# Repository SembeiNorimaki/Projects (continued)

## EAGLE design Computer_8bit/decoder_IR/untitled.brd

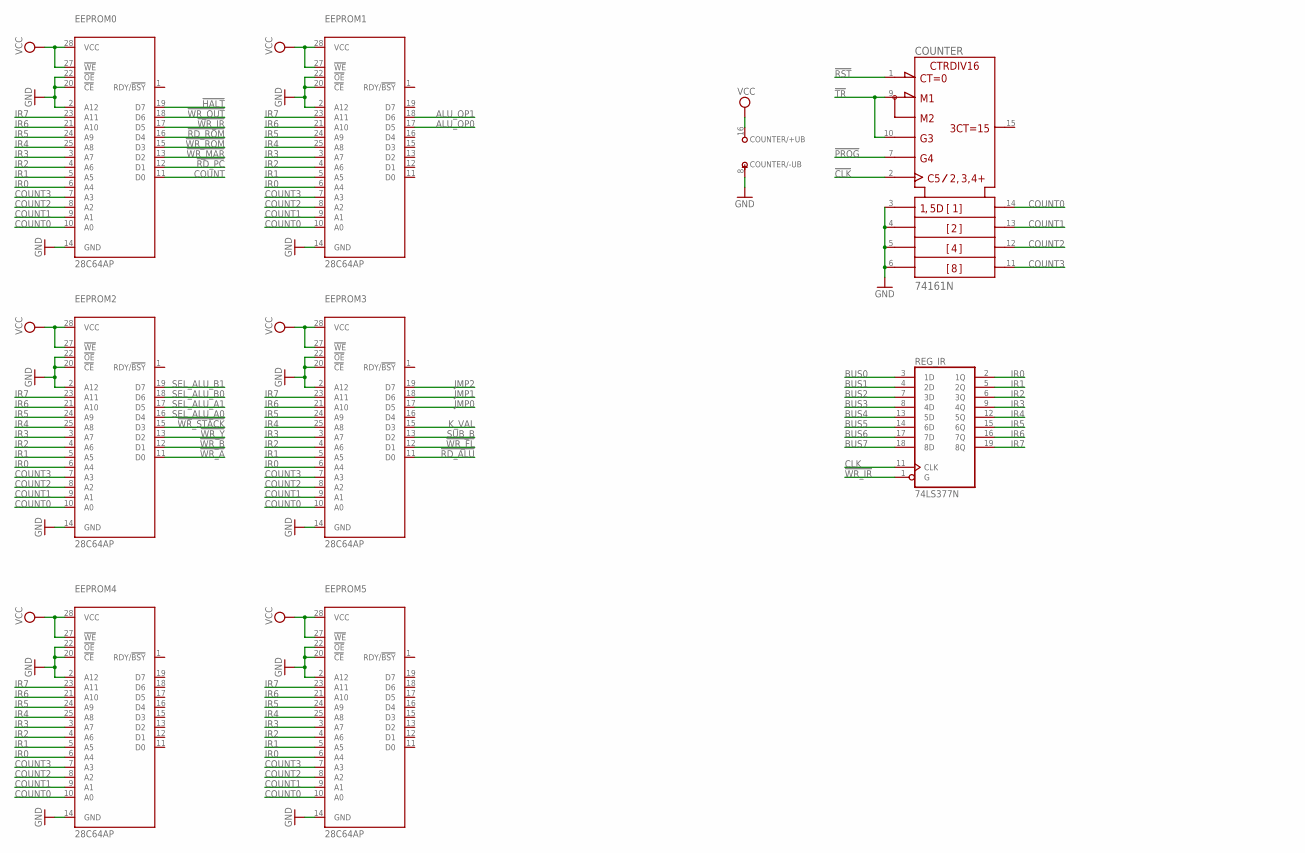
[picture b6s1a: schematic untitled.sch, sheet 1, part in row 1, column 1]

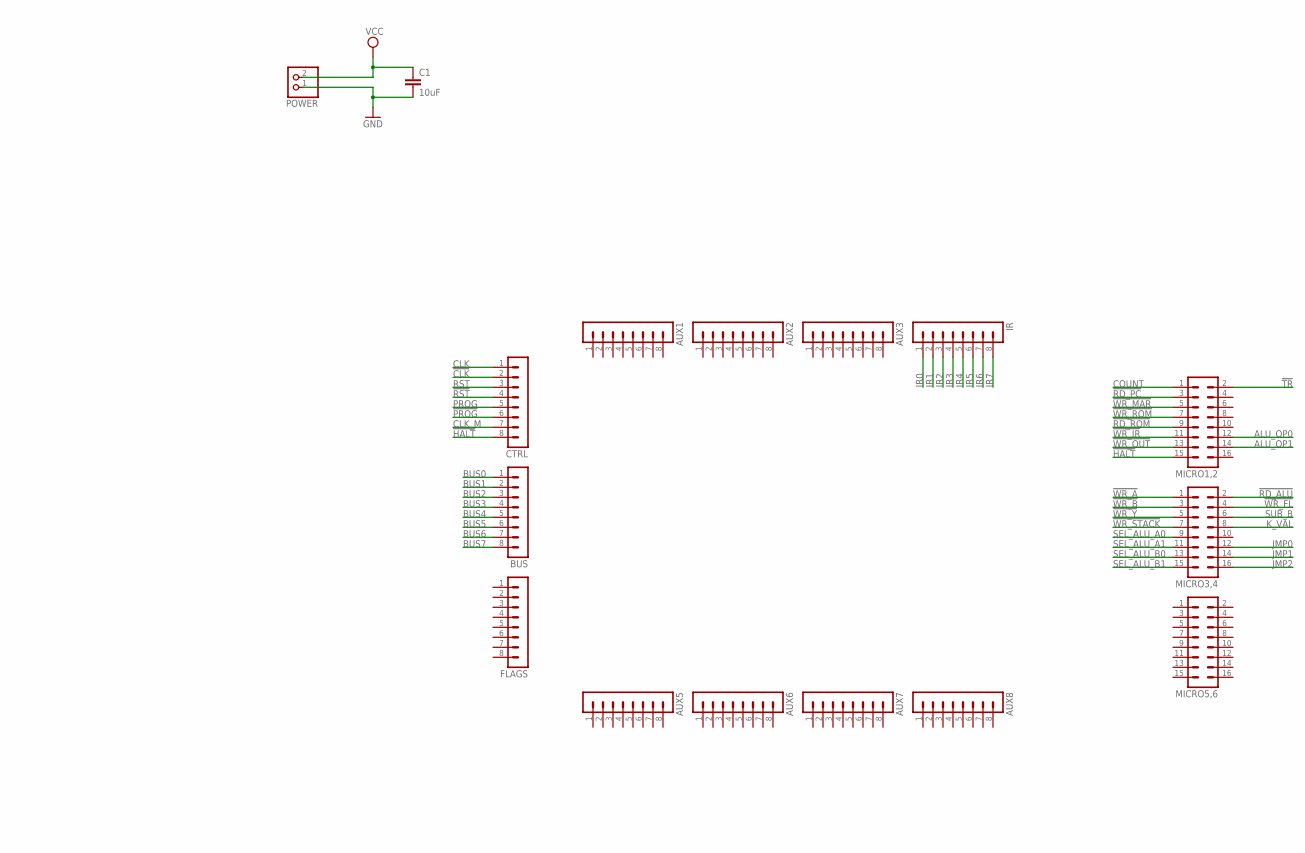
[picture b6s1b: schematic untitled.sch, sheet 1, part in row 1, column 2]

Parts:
AUX1, AUX2, AUX3, AUX5, AUX6, AUX7, AUX8: MA08-1
BUS: MA08-1
C1: 10uF; C025-050X050
COUNTER: 74161N; DIL16
CTRL: MA08-1
EEPROM0, EEPROM1, EEPROM2, EEPROM3, EEPROM4, EEPROM5: 28C64AP; DIL28-6
FLAGS: MA08-1
IR: MA08-1
MICRO1,2, MICRO3,4, MICRO5,6: MA08-2
POWER: PINHD-1X2; 1X02
REG_IR: 74LS377N; DIL20

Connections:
!CLK: COUNTER.2 (CLK), CTRL.2
!HALT: CTRL.8, EEPROM0.19 (D7), MICRO1,2.15
!PROG: COUNTER.7 (ENP), CTRL.6
!RD_ALU: EEPROM3.11 (D0), MICRO3,4.2
!RD_PC: EEPROM0.12 (D1), MICRO1,2.3
!RD_ROM: EEPROM0.16 (D4), MICRO1,2.9
!RST: COUNTER.1 (!CLR), CTRL.4
!TR: COUNTER.9 (!LOAD), COUNTER.10 (ENT), MICRO1,2.2
!WR_A: EEPROM2.11 (D0), MICRO3,4.1
!WR_B: EEPROM2.12 (D1), MICRO3,4.3
!WR_FL: EEPROM3.12 (D1), MICRO3,4.4
!WR_IR: EEPROM0.17 (D5), MICRO1,2.11, REG_IR.1 (G)
!WR_MAR: EEPROM0.13 (D2), MICRO1,2.5
!WR_OUT: EEPROM0.18 (D6), MICRO1,2.13
!WR_ROM: EEPROM0.15 (D3), MICRO1,2.7
!WR_STACK: EEPROM2.15 (D3), MICRO3,4.7
!WR_Y: EEPROM2.13 (D2), MICRO3,4.5
ALU_OP0: EEPROM1.17 (D5), MICRO1,2.12
ALU_OP1: EEPROM1.18 (D6), MICRO1,2.14
BUS0: BUS.1, REG_IR.3 (1D)
BUS1: BUS.2, REG_IR.4 (2D)
BUS2: BUS.3, REG_IR.7 (3D)
BUS3: BUS.4, REG_IR.8 (4D)
BUS4: BUS.5, REG_IR.13 (5D)
BUS5: BUS.6, REG_IR.14 (6D)
BUS6: BUS.7, REG_IR.17 (7D)
BUS7: BUS.8, REG_IR.18 (8D)
CLK: CTRL.1, REG_IR.11 (CLK)
CLK_M: CTRL.7
COUNT: EEPROM0.11 (D0), MICRO1,2.1
COUNT0: COUNTER.14 (QA), EEPROM0.10 (A0), EEPROM1.10 (A0), EEPROM2.10 (A0), EEPROM3.10 (A0), EEPROM4.10 (A0), EEPROM5.10 (A0)
COUNT1: COUNTER.13 (QB), EEPROM0.9 (A1), EEPROM1.9 (A1), EEPROM2.9 (A1), EEPROM3.9 (A1), EEPROM4.9 (A1), EEPROM5.9 (A1)
COUNT2: COUNTER.12 (QC), EEPROM0.8 (A2), EEPROM1.8 (A2), EEPROM2.8 (A2), EEPROM3.8 (A2), EEPROM4.8 (A2), EEPROM5.8 (A2)
COUNT3: COUNTER.11 (QD), EEPROM0.7 (A3), EEPROM1.7 (A3), EEPROM2.7 (A3), EEPROM3.7 (A3), EEPROM4.7 (A3), EEPROM5.7 (A3)
GND: C1.2, COUNTER.3 (A), COUNTER.4 (B), COUNTER.5 (C), COUNTER.6 (D), COUNTER.8 (-UB), EEPROM0.2 (A12), EEPROM0.14 (GND), EEPROM0.20 (!CE), EEPROM0.22 (!OE), EEPROM1.2 (A12), EEPROM1.14 (GND), EEPROM1.20 (!CE), EEPROM1.22 (!OE), EEPROM2.2 (A12), EEPROM2.14 (GND), EEPROM2.20 (!CE), EEPROM2.22 (!OE), EEPROM3.2 (A12), EEPROM3.14 (GND), EEPROM3.20 (!CE), EEPROM3.22 (!OE), EEPROM4.2 (A12), EEPROM4.14 (GND), EEPROM4.20 (!CE), EEPROM4.22 (!OE), EEPROM5.2 (A12), EEPROM5.14 (GND), EEPROM5.20 (!CE), EEPROM5.22 (!OE), POWER.1, REG_IR.10 (GND)
IR0: EEPROM0.6 (A4), EEPROM1.6 (A4), EEPROM2.6 (A4), EEPROM3.6 (A4), EEPROM4.6 (A4), EEPROM5.6 (A4), IR.1, REG_IR.2 (1Q)
IR1: EEPROM0.5 (A5), EEPROM1.5 (A5), EEPROM2.5 (A5), EEPROM3.5 (A5), EEPROM4.5 (A5), EEPROM5.5 (A5), IR.2, REG_IR.5 (2Q)
IR2: EEPROM0.4 (A6), EEPROM1.4 (A6), EEPROM2.4 (A6), EEPROM3.4 (A6), EEPROM4.4 (A6), EEPROM5.4 (A6), IR.3, REG_IR.6 (3Q)
IR3: EEPROM0.3 (A7), EEPROM1.3 (A7), EEPROM2.3 (A7), EEPROM3.3 (A7), EEPROM4.3 (A7), EEPROM5.3 (A7), IR.4, REG_IR.9 (4Q)
IR4: EEPROM0.25 (A8), EEPROM1.25 (A8), EEPROM2.25 (A8), EEPROM3.25 (A8), EEPROM4.25 (A8), EEPROM5.25 (A8), IR.5, REG_IR.12 (5Q)
IR5: EEPROM0.24 (A9), EEPROM1.24 (A9), EEPROM2.24 (A9), EEPROM3.24 (A9), EEPROM4.24 (A9), EEPROM5.24 (A9), IR.6, REG_IR.15 (6Q)
IR6: EEPROM0.21 (A10), EEPROM1.21 (A10), EEPROM2.21 (A10), EEPROM3.21 (A10), EEPROM4.21 (A10), EEPROM5.21 (A10), IR.7, REG_IR.16 (7Q)
IR7: EEPROM0.23 (A11), EEPROM1.23 (A11), EEPROM2.23 (A11), EEPROM3.23 (A11), EEPROM4.23 (A11), EEPROM5.23 (A11), IR.8, REG_IR.19 (8Q)
JMP0: EEPROM3.17 (D5), MICRO3,4.12
JMP1: EEPROM3.18 (D6), MICRO3,4.14
JMP2: EEPROM3.19 (D7), MICRO3,4.16
K_VAL: EEPROM3.15 (D3), MICRO3,4.8
PROG: CTRL.5
RST: CTRL.3
SEL_ALU_A0: EEPROM2.16 (D4), MICRO3,4.9
SEL_ALU_A1: EEPROM2.17 (D5), MICRO3,4.11
SEL_ALU_B0: EEPROM2.18 (D6), MICRO3,4.13
SEL_ALU_B1: EEPROM2.19 (D7), MICRO3,4.15
SUB_B: EEPROM3.13 (D2), MICRO3,4.6
VCC: C1.1, COUNTER.16 (+UB), EEPROM0.27 (!WE), EEPROM0.28 (VCC), EEPROM1.27 (!WE), EEPROM1.28 (VCC), EEPROM2.27 (!WE), EEPROM2.28 (VCC), EEPROM3.27 (!WE), EEPROM3.28 (VCC), EEPROM4.27 (!WE), EEPROM4.28 (VCC), EEPROM5.27 (!WE), EEPROM5.28 (VCC), POWER.2, REG_IR.20 (VCC)

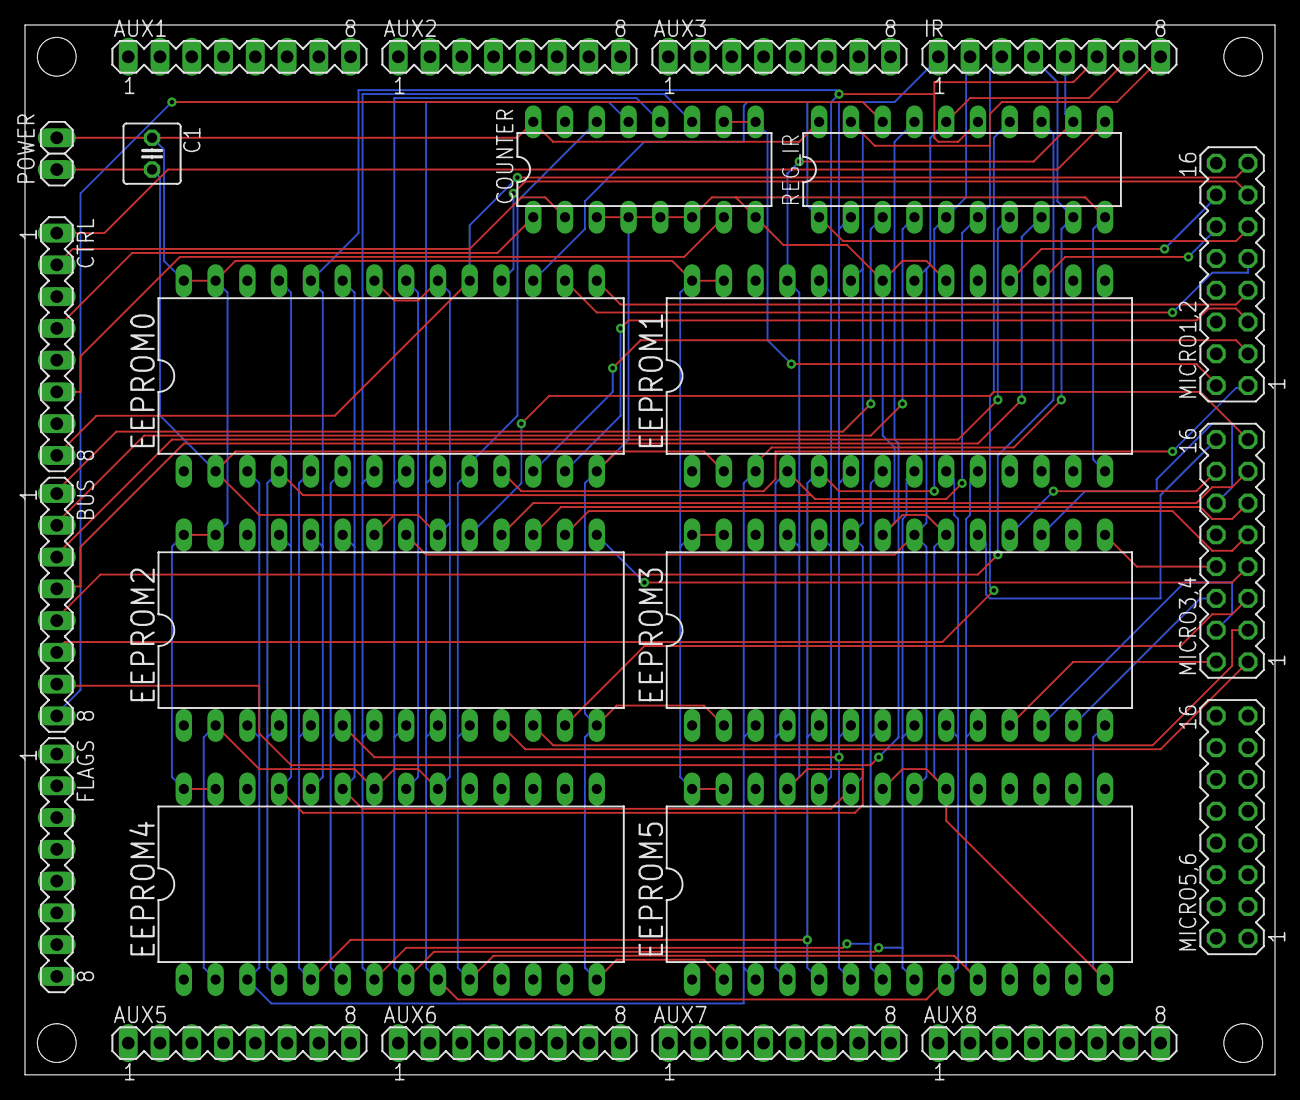
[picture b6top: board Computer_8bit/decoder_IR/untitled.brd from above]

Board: 2 copper layers, 99.9 x 83.9 mm, 24 parts (0 on the bottom side), 52 nets.

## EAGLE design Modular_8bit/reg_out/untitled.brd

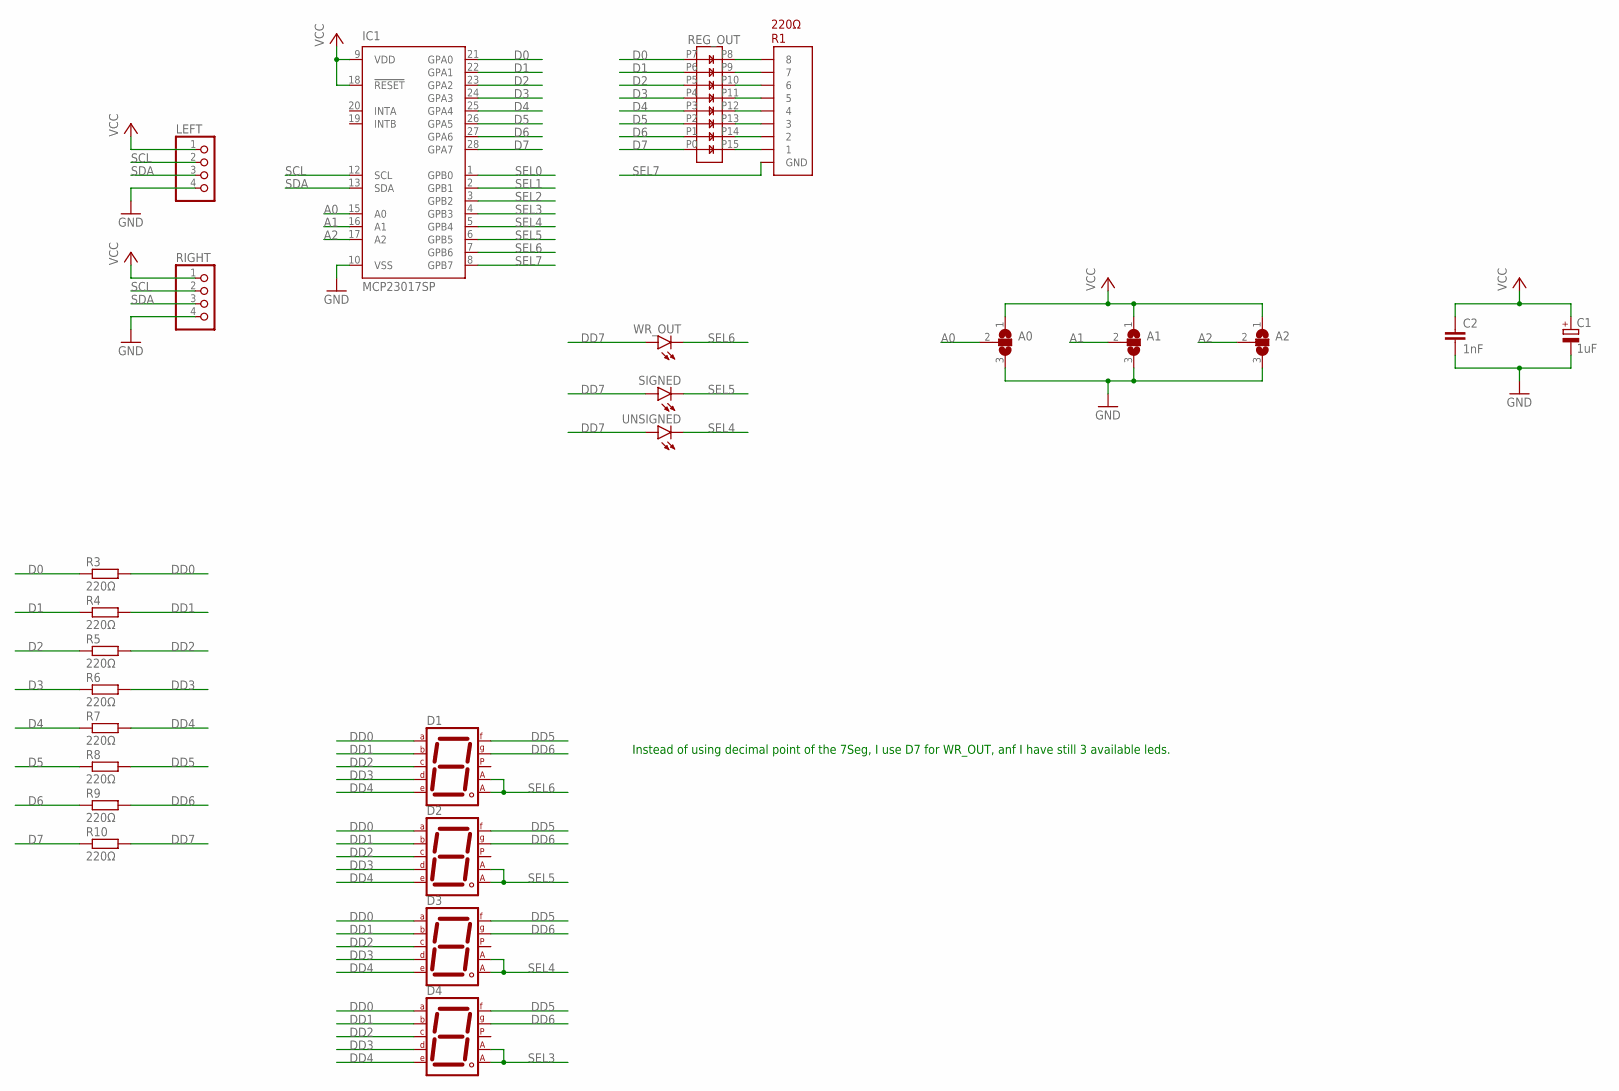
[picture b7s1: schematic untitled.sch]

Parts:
A0, A1, A2: SJ2W; SJ_2
C1: 1uF; E2,5-6
C2: 1nF; C2.5-2
D1, D2, D3, D4: 7SEG-CA; 7SEG-13
IC1: MCP23017SP; DIL28-3
LEFT: PINHD-1X4; 1X04
R1: 220Ω; R_ARRAY_8PIN
R3, R4, R5, R6, R7, R8, R9, R10: 220Ω; 0207/10
REG_OUT: LB8
RIGHT: PINHD-1X4; 1X04
SIGNED: LED3MM
UNSIGNED: LED3MM
WR_OUT: LED3MM

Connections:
A0: A0.2, IC1.15 (A0)
A1: A1.2, IC1.16 (A1)
A2: A2.2, IC1.17 (A2)
D0: IC1.21 (GPA0), R3.1, REG_OUT.P7
D1: IC1.22 (GPA1), R4.1, REG_OUT.P6
D2: IC1.23 (GPA2), R5.1, REG_OUT.P5
D3: IC1.24 (GPA3), R6.1, REG_OUT.P4
D4: IC1.25 (GPA4), R7.1, REG_OUT.P3
D5: IC1.26 (GPA5), R8.1, REG_OUT.P2
D6: IC1.27 (GPA6), R9.1, REG_OUT.P1
D7: IC1.28 (GPA7), R10.1, REG_OUT.P0
DD0: D1.7 (A), D2.7 (A), D3.7 (A), D4.7 (A), R3.2
DD1: D1.6 (B), D2.6 (B), D3.6 (B), D4.6 (B), R4.2
DD2: D1.4 (C), D2.4 (C), D3.4 (C), D4.4 (C), R5.2
DD3: D1.2 (D), D2.2 (D), D3.2 (D), D4.2 (D), R6.2
DD4: D1.1 (E), D2.1 (E), D3.1 (E), D4.1 (E), R7.2
DD5: D1.9 (F), D2.9 (F), D3.9 (F), D4.9 (F), R8.2
DD6: D1.10 (G), D2.10 (G), D3.10 (G), D4.10 (G), R9.2
DD7: R10.2, SIGNED.A, UNSIGNED.A, WR_OUT.A
GND: A0.3, A1.3, A2.3, C1.-, C2.2, IC1.10 (VSS), LEFT.4, RIGHT.4
unnamed: R1.8, REG_OUT.P8
unnamed: R1.7, REG_OUT.P9
unnamed: R1.6, REG_OUT.P10
unnamed: R1.5, REG_OUT.P11
unnamed: R1.4, REG_OUT.P12
unnamed: R1.3, REG_OUT.P13
unnamed: R1.2, REG_OUT.P14
unnamed: R1.1, REG_OUT.P15
SCL: IC1.12 (SCL), LEFT.2, RIGHT.2
SDA: IC1.13 (SDA), LEFT.3, RIGHT.3
SEL0: IC1.1 (GPB0)
SEL1: IC1.2 (GPB1)
SEL2: IC1.3 (GPB2)
SEL3: D4.3 (CA1), D4.8 (CA2), IC1.4 (GPB3)
SEL4: D3.3 (CA1), D3.8 (CA2), IC1.5 (GPB4), UNSIGNED.K (C)
SEL5: D2.3 (CA1), D2.8 (CA2), IC1.6 (GPB5), SIGNED.K (C)
SEL6: D1.3 (CA1), D1.8 (CA2), IC1.7 (GPB6), WR_OUT.K (C)
SEL7: IC1.8 (GPB7), R1.GND
VCC: A0.1, A1.1, A2.1, C1.+, C2.1, IC1.9 (VDD), IC1.18 (!RESET), LEFT.1, RIGHT.1

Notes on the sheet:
Instead of using decimal point of the 7Seg, I use D7 for WR_OUT, anf I have still 3 available leds.

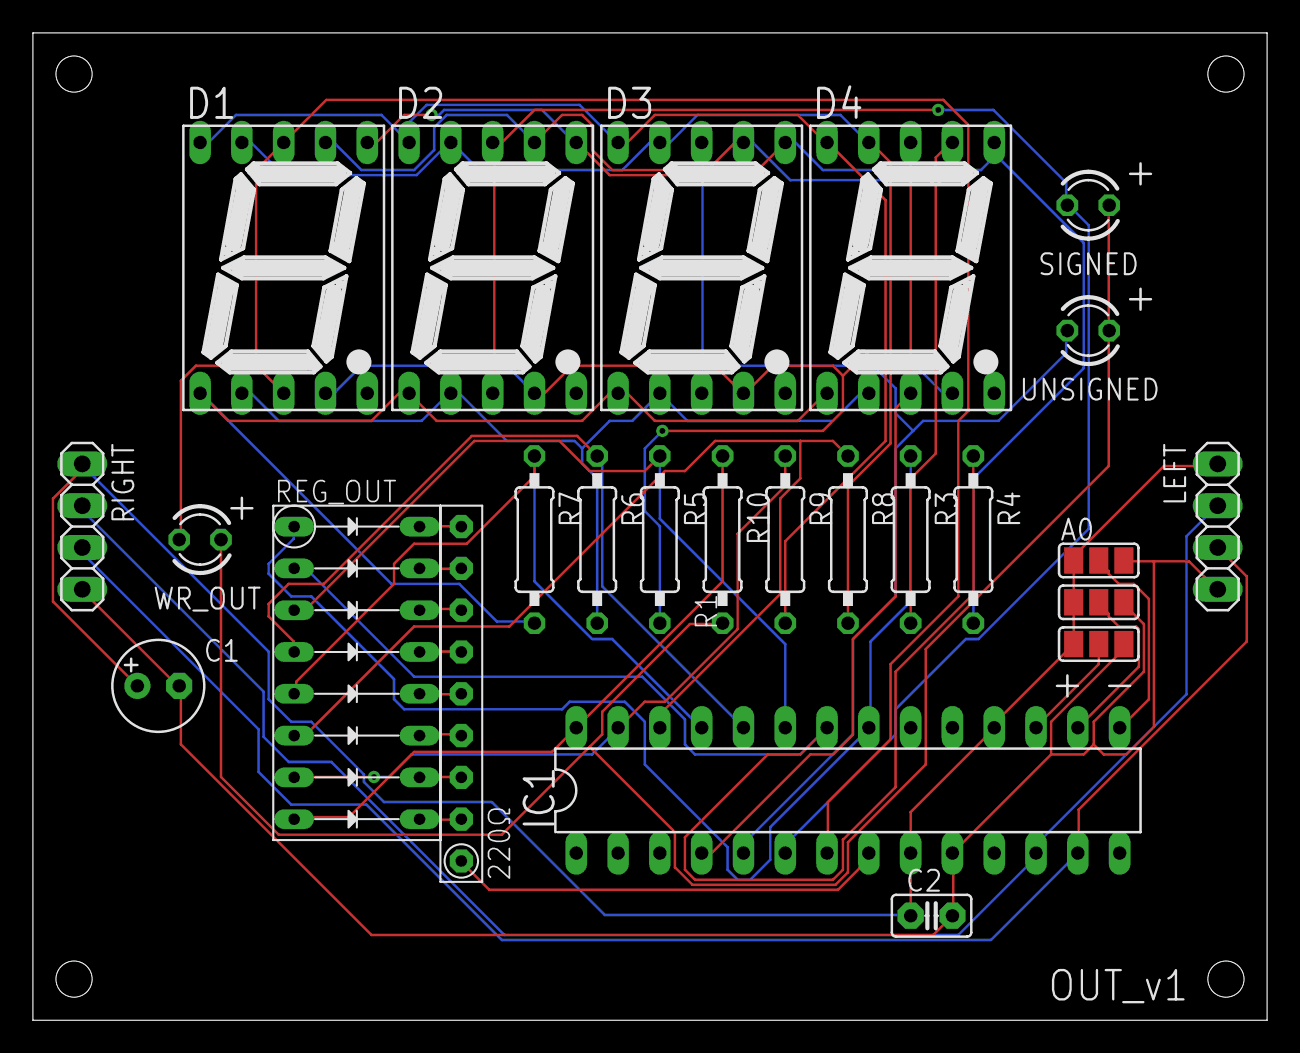
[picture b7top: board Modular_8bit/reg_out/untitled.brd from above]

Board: 2 copper layers, 75.0 x 60.0 mm, 25 parts (0 on the bottom side), 36 nets.

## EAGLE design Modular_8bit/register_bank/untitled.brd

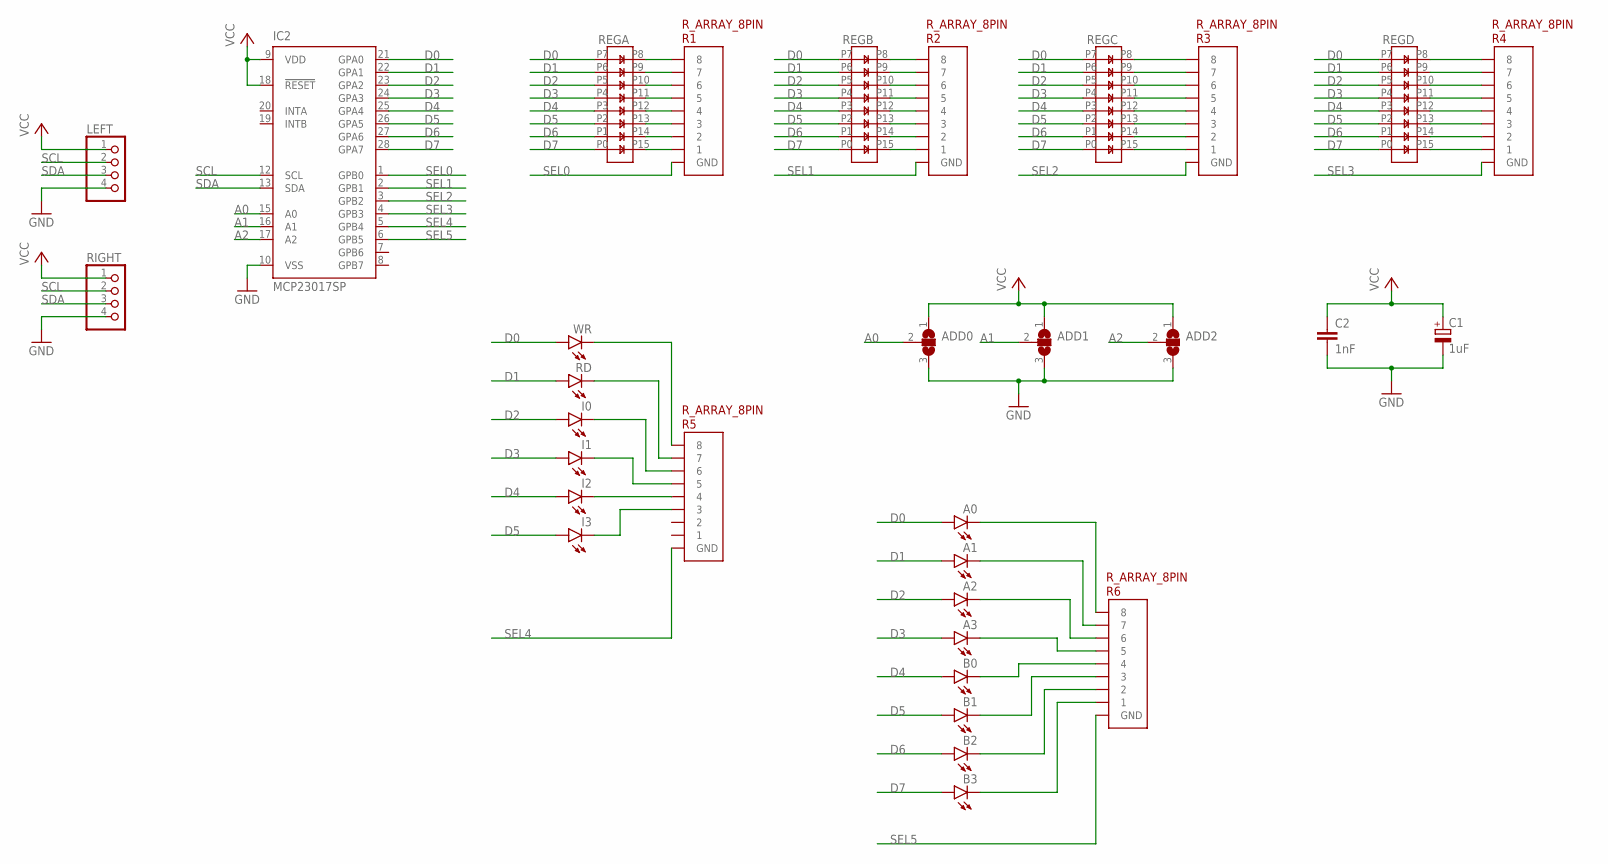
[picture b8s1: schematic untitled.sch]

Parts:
A0, A1, A2, A3: LED3MM
ADD0, ADD1, ADD2: SJ2W; SJ_2
B0, B1, B2, B3: LED3MM
C1: 1uF; E2,5-6
C2: 1nF; C2.5-2
I0, I1, I2, I3: LED3MM
IC2: MCP23017SP; DIL28-3
LEFT: PINHD-1X4; 1X04
R1, R2, R3, R4, R5, R6: R_ARRAY_8PIN
RD: LED3MM
REGA: LB8
REGB: LB8
REGC: LB8
REGD: LB8
RIGHT: PINHD-1X4; 1X04
WR: LED3MM

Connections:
A0: ADD0.2, IC2.15 (A0)
A1: ADD1.2, IC2.16 (A1)
A2: ADD2.2, IC2.17 (A2)
D0: A0.A, IC2.21 (GPA0), REGA.P7, REGB.P7, REGC.P7, REGD.P7, WR.A
D1: A1.A, IC2.22 (GPA1), RD.A, REGA.P6, REGB.P6, REGC.P6, REGD.P6
D2: A2.A, I0.A, IC2.23 (GPA2), REGA.P5, REGB.P5, REGC.P5, REGD.P5
D3: A3.A, I1.A, IC2.24 (GPA3), REGA.P4, REGB.P4, REGC.P4, REGD.P4
D4: B0.A, I2.A, IC2.25 (GPA4), REGA.P3, REGB.P3, REGC.P3, REGD.P3
D5: B1.A, I3.A, IC2.26 (GPA5), REGA.P2, REGB.P2, REGC.P2, REGD.P2
D6: B2.A, IC2.27 (GPA6), REGA.P1, REGB.P1, REGC.P1, REGD.P1
D7: B3.A, IC2.28 (GPA7), REGA.P0, REGB.P0, REGC.P0, REGD.P0
GND: ADD0.3, ADD1.3, ADD2.3, C1.-, C2.2, IC2.10 (VSS), LEFT.4, RIGHT.4
unnamed: R3.8, REGC.P8
unnamed: R3.7, REGC.P9
unnamed: R3.6, REGC.P10
unnamed: R3.5, REGC.P11
unnamed: R3.4, REGC.P12
unnamed: R3.3, REGC.P13
unnamed: R3.2, REGC.P14
unnamed: R3.1, REGC.P15
unnamed: R5.8, WR.K (C)
unnamed: R5.7, RD.K (C)
unnamed: I0.K (C), R5.6
unnamed: I1.K (C), R5.5
unnamed: I2.K (C), R5.4
unnamed: I3.K (C), R5.3
unnamed: R1.8, REGA.P8
unnamed: R1.7, REGA.P9
unnamed: R1.6, REGA.P10
unnamed: R1.5, REGA.P11
unnamed: R1.4, REGA.P12
unnamed: R1.3, REGA.P13
unnamed: R1.2, REGA.P14
unnamed: R1.1, REGA.P15
unnamed: R2.8, REGB.P8
unnamed: R2.7, REGB.P9
unnamed: R2.6, REGB.P10
unnamed: R2.5, REGB.P11
unnamed: R2.4, REGB.P12
unnamed: R2.3, REGB.P13
unnamed: R2.2, REGB.P14
unnamed: R2.1, REGB.P15
unnamed: A0.K (C), R6.8
unnamed: A1.K (C), R6.7
unnamed: A2.K (C), R6.6
unnamed: A3.K (C), R6.5
unnamed: R4.8, REGD.P8
unnamed: R4.7, REGD.P9
unnamed: R4.6, REGD.P10
unnamed: R4.5, REGD.P11
unnamed: R4.4, REGD.P12
unnamed: R4.3, REGD.P13
unnamed: R4.2, REGD.P14
unnamed: R4.1, REGD.P15
unnamed: B0.K (C), R6.4
unnamed: B1.K (C), R6.3
unnamed: B2.K (C), R6.2
unnamed: B3.K (C), R6.1
SCL: IC2.12 (SCL), LEFT.2, RIGHT.2
SDA: IC2.13 (SDA), LEFT.3, RIGHT.3
SEL0: IC2.1 (GPB0), R1.GND
SEL1: IC2.2 (GPB1), R2.GND
SEL2: IC2.3 (GPB2), R3.GND
SEL3: IC2.4 (GPB3), R4.GND
SEL4: IC2.5 (GPB4), R5.GND
SEL5: IC2.6 (GPB5), R6.GND
VCC: ADD0.1, ADD1.1, ADD2.1, C1.+, C2.1, IC2.9 (VDD), IC2.18 (!RESET), LEFT.1, RIGHT.1

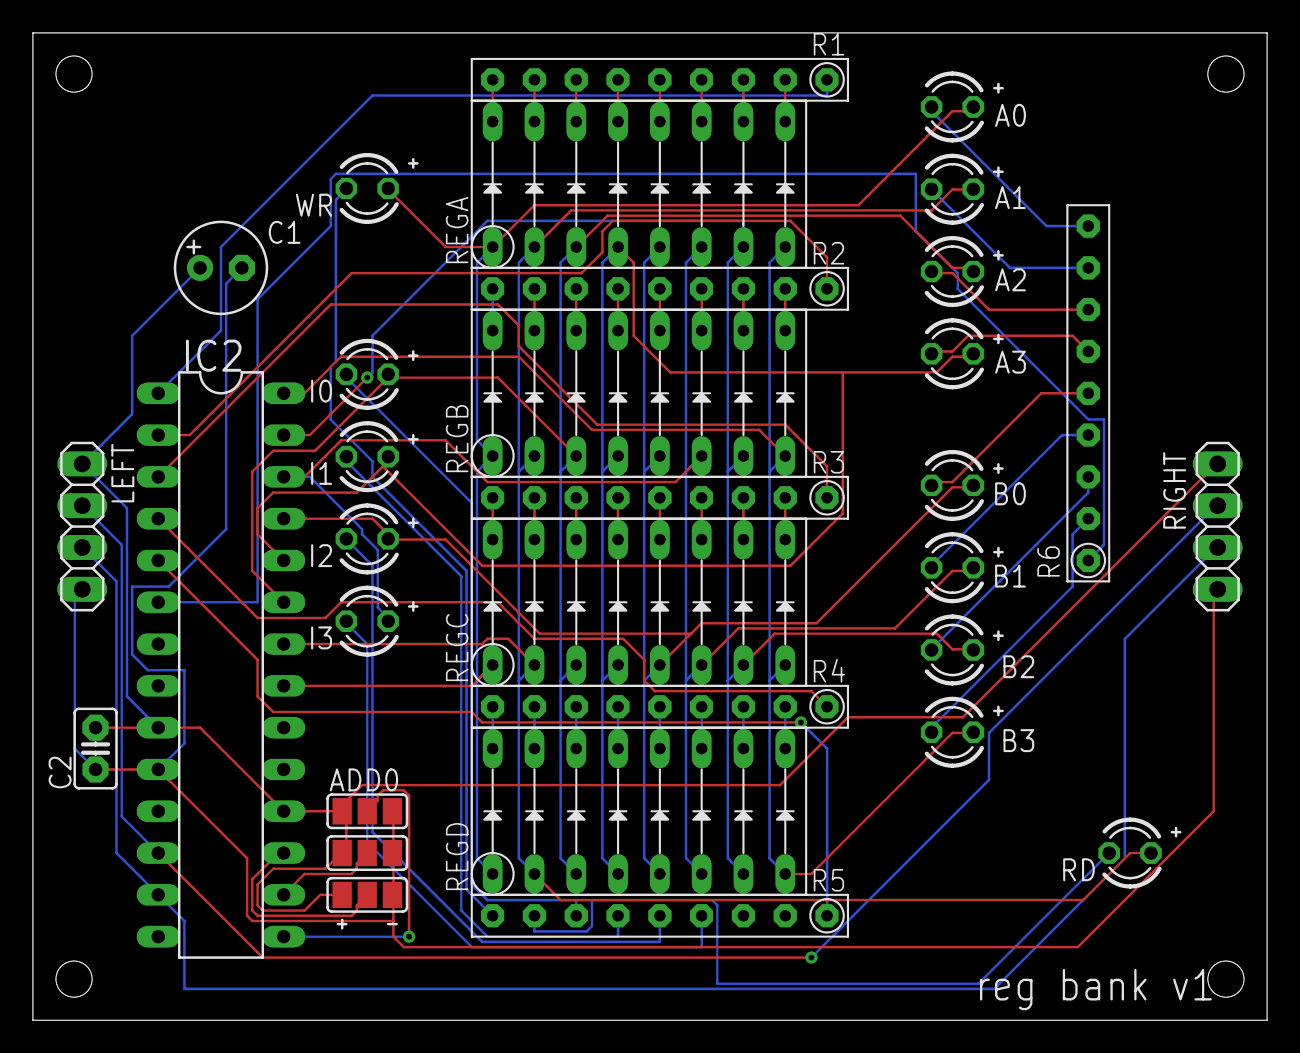
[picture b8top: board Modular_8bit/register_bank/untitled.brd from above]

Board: 2 copper layers, 75.0 x 60.0 mm, 32 parts (0 on the bottom side), 67 nets.

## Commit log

2016-10-26 Github commit test
2016-10-26 test github2
2016-10-26 test github
2017-07-21 Structure
2017-07-26 fritzing
2020-09-16 Cleaned folder
2020-09-16 Dragon Ball
2020-09-16 Hydroponics
2020-09-16 Time glove
2020-09-16 Planetes project
2020-09-16 Modular 8bit
2020-09-16 8bit computer
2020-09-16 MyPrusaBear
2020-09-16 Nile Game
2020-09-16 Robot 4WD
2020-09-16 Prusa
2020-10-05 Added Class Radar
2020-10-08 DragonBall added BT functionalities
2020-10-09 Bluetooth pairing and exchange of data
2020-10-12 Compass methods
2020-11-09 Refactoring, improvements
2020-11-09 Learn German App
2021-01-15 Electronic kit
2021-01-28 Electronic modules implementation
2021-01-29 Modular Kit code
2021-04-01 Bump y18n from 4.0.0 to 4.0.1 in /LearnGerman
    Bumps [y18n](https://github.com/yargs/y18n) from 4.0.0 to 4.0.1.
    - [Release notes](https://github.com/yargs/y18n/releases)
    - [Changelog](https://github.com/yargs/y18n/blob/master/CHANGELOG.md)
    - [Commits](https://github.com/yargs/y18n/commits)
2021-05-08 Bump ua-parser-js from 0.7.22 to 0.7.28 in /LearnGerman
    Bumps [ua-parser-js](https://github.com/faisalman/ua-parser-js) from 0.7.22 to 0.7.28.
    - [Release notes](https://github.com/faisalman/ua-parser-js/releases)
    - [Commits](https://github.com/faisalman/ua-parser-js/compare/0.7.22...0.7.28)
2021-05-11 Bump hosted-git-info from 2.8.8 to 2.8.9 in /LearnGerman
    Bumps [hosted-git-info](https://github.com/npm/hosted-git-info) from 2.8.8 to 2.8.9.
    - [Release notes](https://github.com/npm/hosted-git-info/releases)
    - [Changelog](https://github.com/npm/hosted-git-info/blob/v2.8.9/CHANGELOG.md)
    - [Commits](https://github.com/npm/hosted-git-info/compare/v2.8.8...v2.8.9)
2021-05-11 Bump lodash from 4.17.20 to 4.17.21 in /LearnGerman
    Bumps [lodash](https://github.com/lodash/lodash) from 4.17.20 to 4.17.21.
    - [Release notes](https://github.com/lodash/lodash/releases)
    - [Commits](https://github.com/lodash/lodash/compare/4.17.20...4.17.21)
2021-06-12 Bump glob-parent from 5.1.1 to 5.1.2 in /LearnGerman
    Bumps [glob-parent](https://github.com/gulpjs/glob-parent) from 5.1.1 to 5.1.2.
    - [Release notes](https://github.com/gulpjs/glob-parent/releases)
    - [Changelog](https://github.com/gulpjs/glob-parent/blob/main/CHANGELOG.md)
    - [Commits](https://github.com/gulpjs/glob-parent/compare/v5.1.1...v5.1.2)
    ---
    updated-dependencies:
2021-07-20 Bump react-native from 0.63.2 to 0.64.1 in /LearnGerman
    Bumps [react-native](https://github.com/facebook/react-native) from 0.63.2 to 0.64.1.
    - [Release notes](https://github.com/facebook/react-native/releases)
    - [Changelog](https://github.com/facebook/react-native/blob/main/Releases.md)
    - [Commits](https://github.com/facebook/react-native/compare/v0.63.2...v0.64.1)
    ---
    updated-dependencies:
2021-08-12 Bump path-parse from 1.0.6 to 1.0.7 in /LearnGerman
    Bumps [path-parse](https://github.com/jbgutierrez/path-parse) from 1.0.6 to 1.0.7.
    - [Release notes](https://github.com/jbgutierrez/path-parse/releases)
    - [Commits](https://github.com/jbgutierrez/path-parse/commits/v1.0.7)
    ---
    updated-dependencies:
    - dependency-name: path-parse
2021-09-22 Bump tmpl from 1.0.4 to 1.0.5 in /LearnGerman
    Bumps [tmpl](https://github.com/daaku/nodejs-tmpl) from 1.0.4 to 1.0.5.
    - [Release notes](https://github.com/daaku/nodejs-tmpl/releases)
    - [Commits](https://github.com/daaku/nodejs-tmpl/commits/v1.0.5)
    ---
    updated-dependencies:
    - dependency-name: tmpl
2022-01-22 Bump nanoid from 3.1.12 to 3.2.0 in /LearnGerman
    Bumps [nanoid](https://github.com/ai/nanoid) from 3.1.12 to 3.2.0.
    - [Release notes](https://github.com/ai/nanoid/releases)
    - [Changelog](https://github.com/ai/nanoid/blob/main/CHANGELOG.md)
    - [Commits](https://github.com/ai/nanoid/compare/3.1.12...3.2.0)
    ---
    updated-dependencies:
2022-03-02 Bump plist from 3.0.1 to 3.0.4 in /LearnGerman
    Bumps [plist](https://github.com/TooTallNate/node-plist) from 3.0.1 to 3.0.4.
    - [Release notes](https://github.com/TooTallNate/node-plist/releases)
    - [Changelog](https://github.com/TooTallNate/plist.js/blob/master/History.md)
    - [Commits](https://github.com/TooTallNate/node-plist/commits)
    ---
    updated-dependencies:
2022-03-28 Bump minimist from 1.2.5 to 1.2.6 in /LearnGerman
    Bumps [minimist](https://github.com/substack/minimist) from 1.2.5 to 1.2.6.
    - [Release notes](https://github.com/substack/minimist/releases)
    - [Commits](https://github.com/substack/minimist/compare/1.2.5...1.2.6)
    ---
    updated-dependencies:
    - dependency-name: minimist
2022-04-29 Bump async from 2.6.3 to 2.6.4 in /LearnGerman
    Bumps [async](https://github.com/caolan/async) from 2.6.3 to 2.6.4.
    - [Release notes](https://github.com/caolan/async/releases)
    - [Changelog](https://github.com/caolan/async/blob/v2.6.4/CHANGELOG.md)
    - [Commits](https://github.com/caolan/async/compare/v2.6.3...v2.6.4)
    ---
    updated-dependencies:
2022-06-02 Bump simple-plist from 1.1.0 to 1.3.1 in /LearnGerman
    Bumps [simple-plist](https://github.com/wollardj/simple-plist) from 1.1.0 to 1.3.1.
    - [Release notes](https://github.com/wollardj/simple-plist/releases)
    - [Commits](https://github.com/wollardj/simple-plist/compare/1.1.0...v1.3.1)
    ---
    updated-dependencies:
    - dependency-name: simple-plist
2022-10-12 Bump xmldom and plist in /LearnGerman
    Removes [xmldom](https://github.com/xmldom/xmldom). It's no longer used after updating ancestor dependency [plist](https://github.com/TooTallNate/node-plist). These dependencies need to be updated to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
    Removes `xmldom`
    Updates `plist` from 3.0.1 to 3.0.6
    - [Release notes](https://github.com/TooTallNate/node-plist/releases)
    - [Changelog](https://github.com/TooTallNate/plist.js/blob/master/History.md)
    - [Commits](https://github.com/TooTallNate/node-plist/commits)
2022-10-21 Bump react-native-reanimated from 1.13.1 to 2.10.0 in /LearnGerman
    Bumps [react-native-reanimated](https://github.com/software-mansion/react-native-reanimated) from 1.13.1 to 2.10.0.
    - [Release notes](https://github.com/software-mansion/react-native-reanimated/releases)
    - [Commits](https://github.com/software-mansion/react-native-reanimated/compare/1.13.1...2.10.0)
    ---
    updated-dependencies:
    - dependency-name: react-native-reanimated
2022-11-10 Bump minimatch from 3.0.4 to 3.1.2 in /LearnGerman
    Bumps [minimatch](https://github.com/isaacs/minimatch) from 3.0.4 to 3.1.2.
    - [Release notes](https://github.com/isaacs/minimatch/releases)
    - [Commits](https://github.com/isaacs/minimatch/compare/v3.0.4...v3.1.2)
    ---
    updated-dependencies:
    - dependency-name: minimatch
2022-12-07 Bump decode-uri-component from 0.2.0 to 0.2.2 in /LearnGerman
    Bumps [decode-uri-component](https://github.com/SamVerschueren/decode-uri-component) from 0.2.0 to 0.2.2.
    - [Release notes](https://github.com/SamVerschueren/decode-uri-component/releases)
    - [Commits](https://github.com/SamVerschueren/decode-uri-component/compare/v0.2.0...v0.2.2)
    ---
    updated-dependencies:
    - dependency-name: decode-uri-component
2022-12-11 Bump qs from 6.5.2 to 6.5.3 in /LearnGerman
    Bumps [qs](https://github.com/ljharb/qs) from 6.5.2 to 6.5.3.
    - [Release notes](https://github.com/ljharb/qs/releases)
    - [Changelog](https://github.com/ljharb/qs/blob/main/CHANGELOG.md)
    - [Commits](https://github.com/ljharb/qs/compare/v6.5.2...v6.5.3)
    ---
    updated-dependencies:
2023-01-06 Bump json5 from 2.1.3 to 2.2.3 in /LearnGerman
    Bumps [json5](https://github.com/json5/json5) from 2.1.3 to 2.2.3.
    - [Release notes](https://github.com/json5/json5/releases)
    - [Changelog](https://github.com/json5/json5/blob/main/CHANGELOG.md)
    - [Commits](https://github.com/json5/json5/compare/v2.1.3...v2.2.3)
    ---
    updated-dependencies:
